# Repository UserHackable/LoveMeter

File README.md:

## LoveMeter 

### Board dimensions

* (390000, 110000) original units
* (3.9000, 1.1000) inches
* (99.0600, 27.9400) mm

[gerbers](%*_gerber.zip)

| Front | Back |
| --- | --- |
|  |  |

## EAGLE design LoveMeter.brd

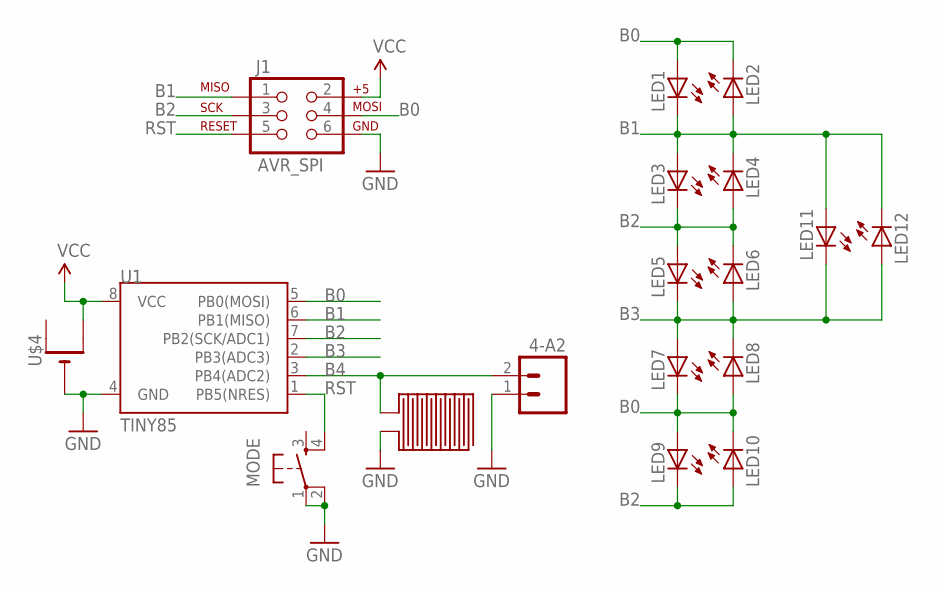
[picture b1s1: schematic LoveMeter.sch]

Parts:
4-A2: M02PTH; 1X02
J1: AVR_SPI; 2X3-NS
LED1, LED2, LED3, LED4, LED5, LED6, LED7, LED8, LED9, LED10, LED11, LED12: LEDOVAL; LED-OVAL
MODE: TAC_SWITCHPTH; TACTILE-PTH
U1: TINY85; DIP08
U$3: THUMB_PAD
U$4: CR2032STRAP; CR2032_STRAP

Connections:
B0: J1.4 (MOSI), LED1.ANODE (A), LED2.CATHODE (C), LED7.CATHODE (C), LED8.ANODE (A), LED9.ANODE (A), LED10.CATHODE (C), U1.5 (PB0(MOSI))
B1: J1.1 (MISO), LED1.CATHODE (C), LED2.ANODE (A), LED3.ANODE (A), LED4.CATHODE (C), LED11.ANODE (A), LED12.CATHODE (C), U1.6 (PB1(MISO))
B2: J1.3 (SCK), LED3.CATHODE (C), LED4.ANODE (A), LED5.ANODE (A), LED6.CATHODE (C), LED9.CATHODE (C), LED10.ANODE (A), U1.7 (PB2(SCK/ADC1))
B3: LED5.CATHODE (C), LED6.ANODE (A), LED7.ANODE (A), LED8.CATHODE (C), LED11.CATHODE (C), LED12.ANODE (A), U1.2 (PB3(ADC3))
B4: 4-A2.2, U1.3 (PB4(ADC2)), U$3.2
GND: 4-A2.1, J1.6 (GND), MODE.1, MODE.2, U1.4 (GND), U$3.1, U$4.-
RST: J1.5 (RST), MODE.4, U1.1 (PB5(NRES))
VCC: J1.2 (V+), U1.8 (VCC), U$4.+2 (+1)

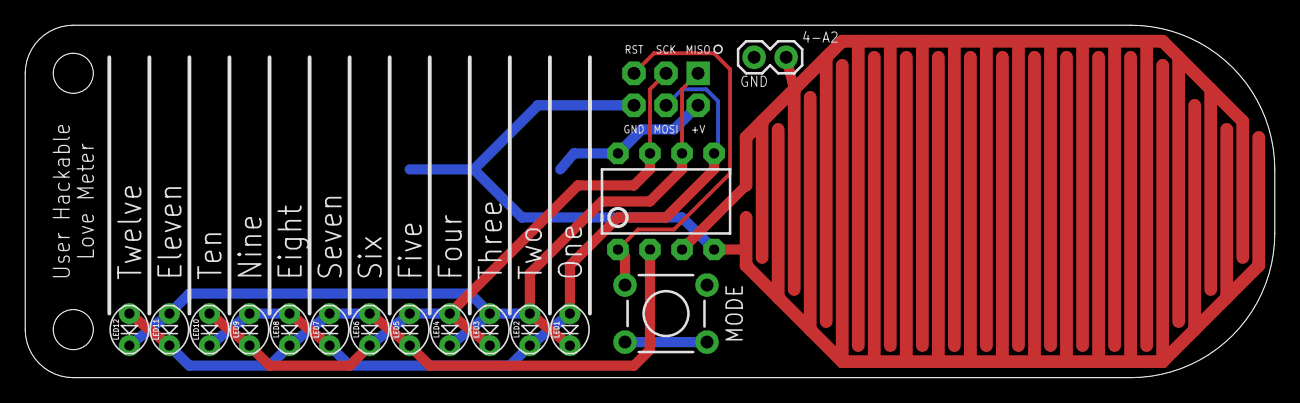
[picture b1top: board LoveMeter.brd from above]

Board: 2 copper layers, 99.1 x 27.9 mm, 18 parts (1 on the bottom side), 8 nets.

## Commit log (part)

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2016-04-06 updating images
2016-04-07 from Makefile

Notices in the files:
parts and their libraries:
SparkFun-Aesthetics: Licensing: Creative Commons ShareAlike 4.0 International - https://creativecommons.org/licenses/by-sa/4.0
